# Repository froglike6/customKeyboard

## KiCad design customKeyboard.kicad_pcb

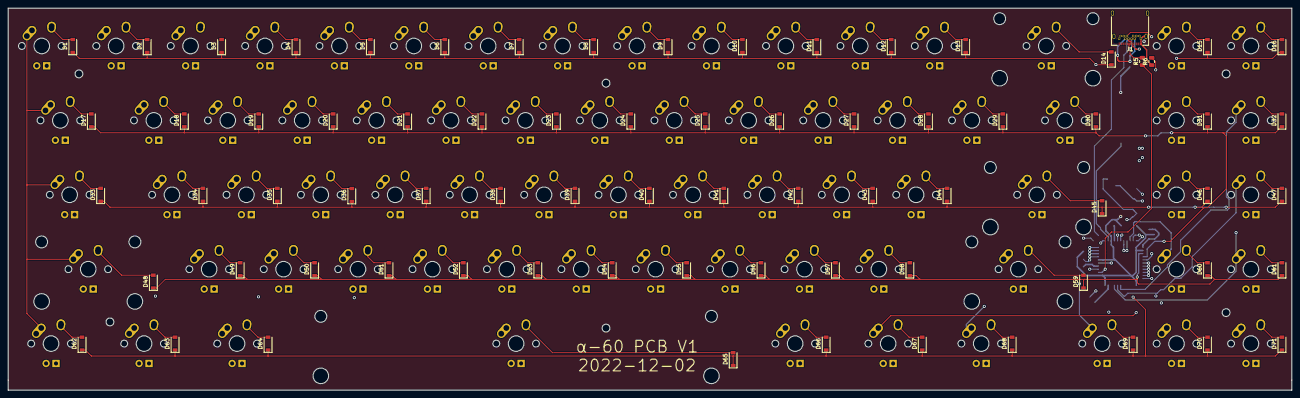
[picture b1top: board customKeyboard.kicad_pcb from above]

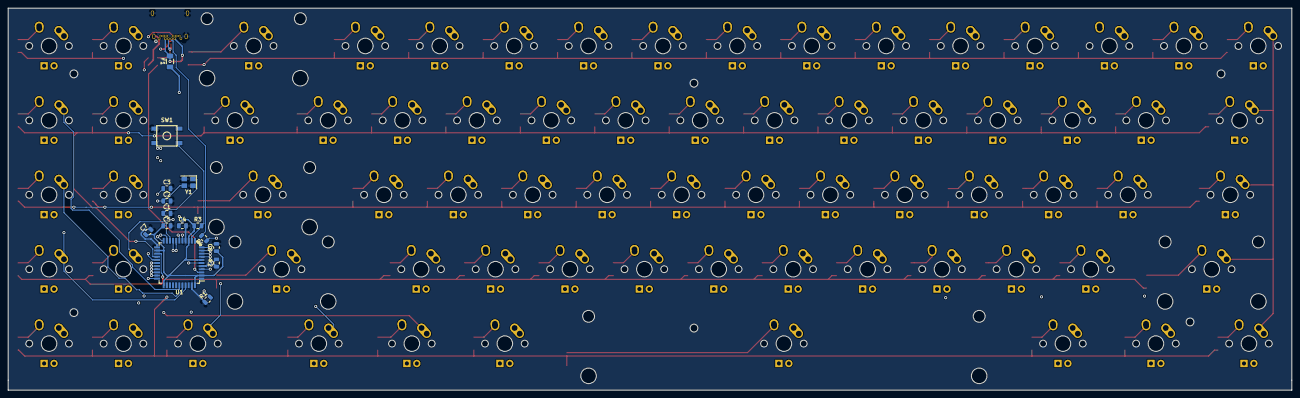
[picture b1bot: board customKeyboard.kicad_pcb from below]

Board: 4 copper layers, 328.6 x 97.8 mm, 160 parts (15 on the bottom side), 106 nets.

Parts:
C1, C2: 22pF; C_0805_2012Metric
C3: 1uF; C_0805_2012Metric
C4, C5, C6: 0.1uF; C_0805_2012Metric
C7: 10uF; C_0805_2012Metric
D1, D2, D3, D4, D5, D6, D7, D8, D9, D10, D11, D12, D13, D14, D15, D16, D17, D18, D19, D20, D21, D22, D23, D24, D25, D26, D27, D28, D29, D30, D31, D32, D33, D34, D35, D36, D37, D38, D39, D40, D41, D42, D43, D44, D45, D46, D47, D48, D49, D50, D51, D52, D53, D54, D55, D56, D57, D58, D59, D60, D61, D62, D63, D64, D65, D66, D67, D68, D69, D70, D71: D_Small; D_SOD-123
F1: 500mA; Fuse_1206_3216Metric
J1: USB_C_Receptacle_USB2.0; USB_C_Receptacle_Amphenol_12401548E4-2A
MX1, MX2, MX3, MX4, MX5, MX6, MX7, MX8, MX9, MX10, MX11, MX12, MX13, MX15, MX16, MX18, MX19, MX20, MX21, MX22, MX23, MX24, MX25, MX26, MX27, MX28, MX29, MX31, MX32, MX34, MX35, MX36, MX37, MX38, MX39, MX40, MX41, MX42, MX43, MX44, MX46, MX47, MX49, MX50, MX51, MX52, MX53, MX54, MX55, MX56, MX57, MX58, MX60, MX61, MX69, MX70, MX71: MX-NoLED; MX-1U
MX14: MX-NoLED; MX-2U
MX17, MX30: MX-NoLED; MX-1.5U
MX33: MX-NoLED; MX-1.75U
MX45, MX48: MX-NoLED; MX-2.25U
MX59: MX-NoLED; MX-2.75U
MX62, MX63, MX64, MX66, MX67, MX68: MX-NoLED; MX-1.25U
MX65: MX-NoLED; MX-6.25U
R1, R2: 5.1k; R_0805_2012Metric
R3, R6: 10k; R_0805_2012Metric
R4, R5: 22; R_0805_2012Metric
SW1: SW_Push; SKQG-1155865
U1: ATmega32U4-AU; TQFP-44_10x10mm_P0.8mm
Y1: 16MHz; Crystal_SMD_3225-4Pin_3.2x2.5mm

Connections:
+5V: C4.1, C5.1, C6.1, C7.1, F1.1, R3.1, U1.2, U1.7, U1.14, U1.24, U1.34, U1.44
COL0: MX1.1, MX17.1, MX33.1, MX48.1, MX62.1, U1.8
COL1: MX2.1, MX18.1, MX34.1, MX49.1, MX63.1, U1.9
COL2: MX3.1, MX19.1, MX35.1, MX50.1, MX64.1, U1.10
COL3: MX4.1, MX20.1, MX36.1, MX51.1, MX65.1, U1.11
COL4: MX5.1, MX21.1, MX37.1, MX52.1, MX66.1, U1.28
COL5: MX6.1, MX22.1, MX38.1, MX53.1, MX67.1, U1.29
COL6: MX7.1, MX23.1, MX39.1, MX54.1, MX68.1, U1.30
COL7: MX8.1, MX24.1, MX40.1, MX55.1, MX69.1, U1.12
COL8: MX9.1, MX25.1, MX41.1, MX56.1, MX70.1, U1.31
COL9: MX10.1, MX26.1, MX42.1, MX57.1, MX71.1, U1.32
COL10: MX11.1, MX27.1, MX43.1, MX58.1, U1.18
COL11: MX12.1, MX28.1, MX44.1, MX59.1, U1.19
COL12: MX13.1, MX29.1, MX45.1, MX60.1, U1.20
COL13: MX14.1, MX30.1, MX46.1, MX61.1, U1.41
COL14: MX15.1, MX31.1, MX47.1, U1.40
COL15: MX16.1, MX32.1, U1.39
D+: J1.A6, J1.B6, R4.2
D-: J1.A7, J1.B7, R5.2
GND: C1.2, C2.2, C3.2, C4.2, C5.2, C6.2, C7.2, J1.A1, J1.A12, J1.B1, J1.B12, J1.S1, R1.1, R2.1, R6.1, SW1.1, U1.5, U1.15, U1.23, U1.35, U1.43, Y1.2, Y1.4
unnamed: C1.1, U1.17, Y1.1
unnamed: C2.1, U1.16, Y1.3
unnamed: C3.1, U1.6
unnamed: D1.2, MX1.2
unnamed: D2.2, MX2.2
unnamed: D3.2, MX3.2
unnamed: D4.2, MX4.2
unnamed: D5.2, MX5.2
unnamed: D6.2, MX6.2
unnamed: D7.2, MX7.2
unnamed: D8.2, MX8.2
unnamed: D9.2, MX9.2
unnamed: D10.2, MX10.2
unnamed: D11.2, MX11.2
unnamed: D12.2, MX12.2
unnamed: D13.2, MX13.2
unnamed: D14.2, MX14.2
unnamed: D15.2, MX15.2
unnamed: D16.2, MX16.2
unnamed: D17.2, MX17.2
unnamed: D18.2, MX18.2
unnamed: D19.2, MX19.2
unnamed: D20.2, MX20.2
unnamed: D21.2, MX21.2
unnamed: D22.2, MX22.2
unnamed: D23.2, MX23.2
unnamed: D24.2, MX24.2
unnamed: D25.2, MX25.2
unnamed: D26.2, MX26.2
unnamed: D27.2, MX27.2
unnamed: D28.2, MX28.2
unnamed: D29.2, MX29.2
unnamed: D30.2, MX30.2
unnamed: D31.2, MX31.2
unnamed: D32.2, MX32.2
unnamed: D33.2, MX33.2
unnamed: D34.2, MX34.2
unnamed: D35.2, MX35.2
unnamed: D36.2, MX36.2
unnamed: D37.2, MX37.2
unnamed: D38.2, MX38.2
unnamed: D39.2, MX39.2
unnamed: D40.2, MX40.2
unnamed: D41.2, MX41.2
unnamed: D42.2, MX42.2
unnamed: D43.2, MX43.2
unnamed: D44.2, MX44.2
unnamed: D45.2, MX45.2
unnamed: D46.2, MX46.2
unnamed: D47.2, MX47.2
unnamed: D48.2, MX48.2
unnamed: D49.2, MX49.2
unnamed: D50.2, MX50.2
unnamed: D51.2, MX51.2
unnamed: D52.2, MX52.2
unnamed: D53.2, MX53.2
unnamed: D54.2, MX54.2
unnamed: D55.2, MX55.2
unnamed: D56.2, MX56.2
unnamed: D57.2, MX57.2
unnamed: D58.2, MX58.2
unnamed: D59.2, MX59.2
unnamed: D60.2, MX60.2
unnamed: D61.2, MX61.2
unnamed: D62.2, MX62.2
unnamed: D63.2, MX63.2
unnamed: D64.2, MX64.2
unnamed: D65.2, MX65.2
unnamed: D66.2, MX66.2
unnamed: D67.2, MX67.2
unnamed: D68.2, MX68.2
unnamed: D69.2, MX69.2
unnamed: D70.2, MX70.2
unnamed: D71.2, MX71.2
unnamed: J1.A5, R1.2
unnamed: J1.B5, R2.2
unnamed: R3.2, SW1.2, U1.13
unnamed: R4.1, U1.4
unnamed: R5.1, U1.3
unnamed: R6.2, U1.33
ROW0: D1.1, D2.1, D3.1, D4.1, D5.1, D6.1, D7.1, D8.1, D9.1, D10.1, D11.1, D12.1, D13.1, D14.1, D15.1, D16.1, U1.27
ROW1: D17.1, D18.1, D19.1, D20.1, D21.1, D22.1, D23.1, D24.1, D25.1, D26.1, D27.1, D28.1, D29.1, D30.1, D31.1, D32.1, U1.26
ROW2: D33.1, D34.1, D35.1, D36.1, D37.1, D38.1, D39.1, D40.1, D41.1, D42.1, D43.1, D44.1, D45.1, D46.1, D47.1, U1.22
ROW3: D48.1, D49.1, D50.1, D51.1, D52.1, D53.1, D54.1, D55.1, D56.1, D57.1, D58.1, D59.1, D60.1, D61.1, U1.25
ROW4: D62.1, D63.1, D64.1, D65.1, D66.1, D67.1, D68.1, D69.1, D70.1, D71.1, U1.21
VCC: F1.2, J1.A4, J1.A9, J1.B4, J1.B9

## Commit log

2022-11-29 Edited directory
2022-11-29 Add submodule
2022-11-29 Add footprint libraries
2022-11-29 Add row col
2022-11-30 Completed Switches Placing
2022-11-30 Placed Diode 1~11
2022-11-30 Placing complete and Replaced USB-C
2022-12-01 ROW and COL0 complete
2022-12-02 80% Complete
2022-12-02 Complete!
2022-12-02 Add keyboard design file
